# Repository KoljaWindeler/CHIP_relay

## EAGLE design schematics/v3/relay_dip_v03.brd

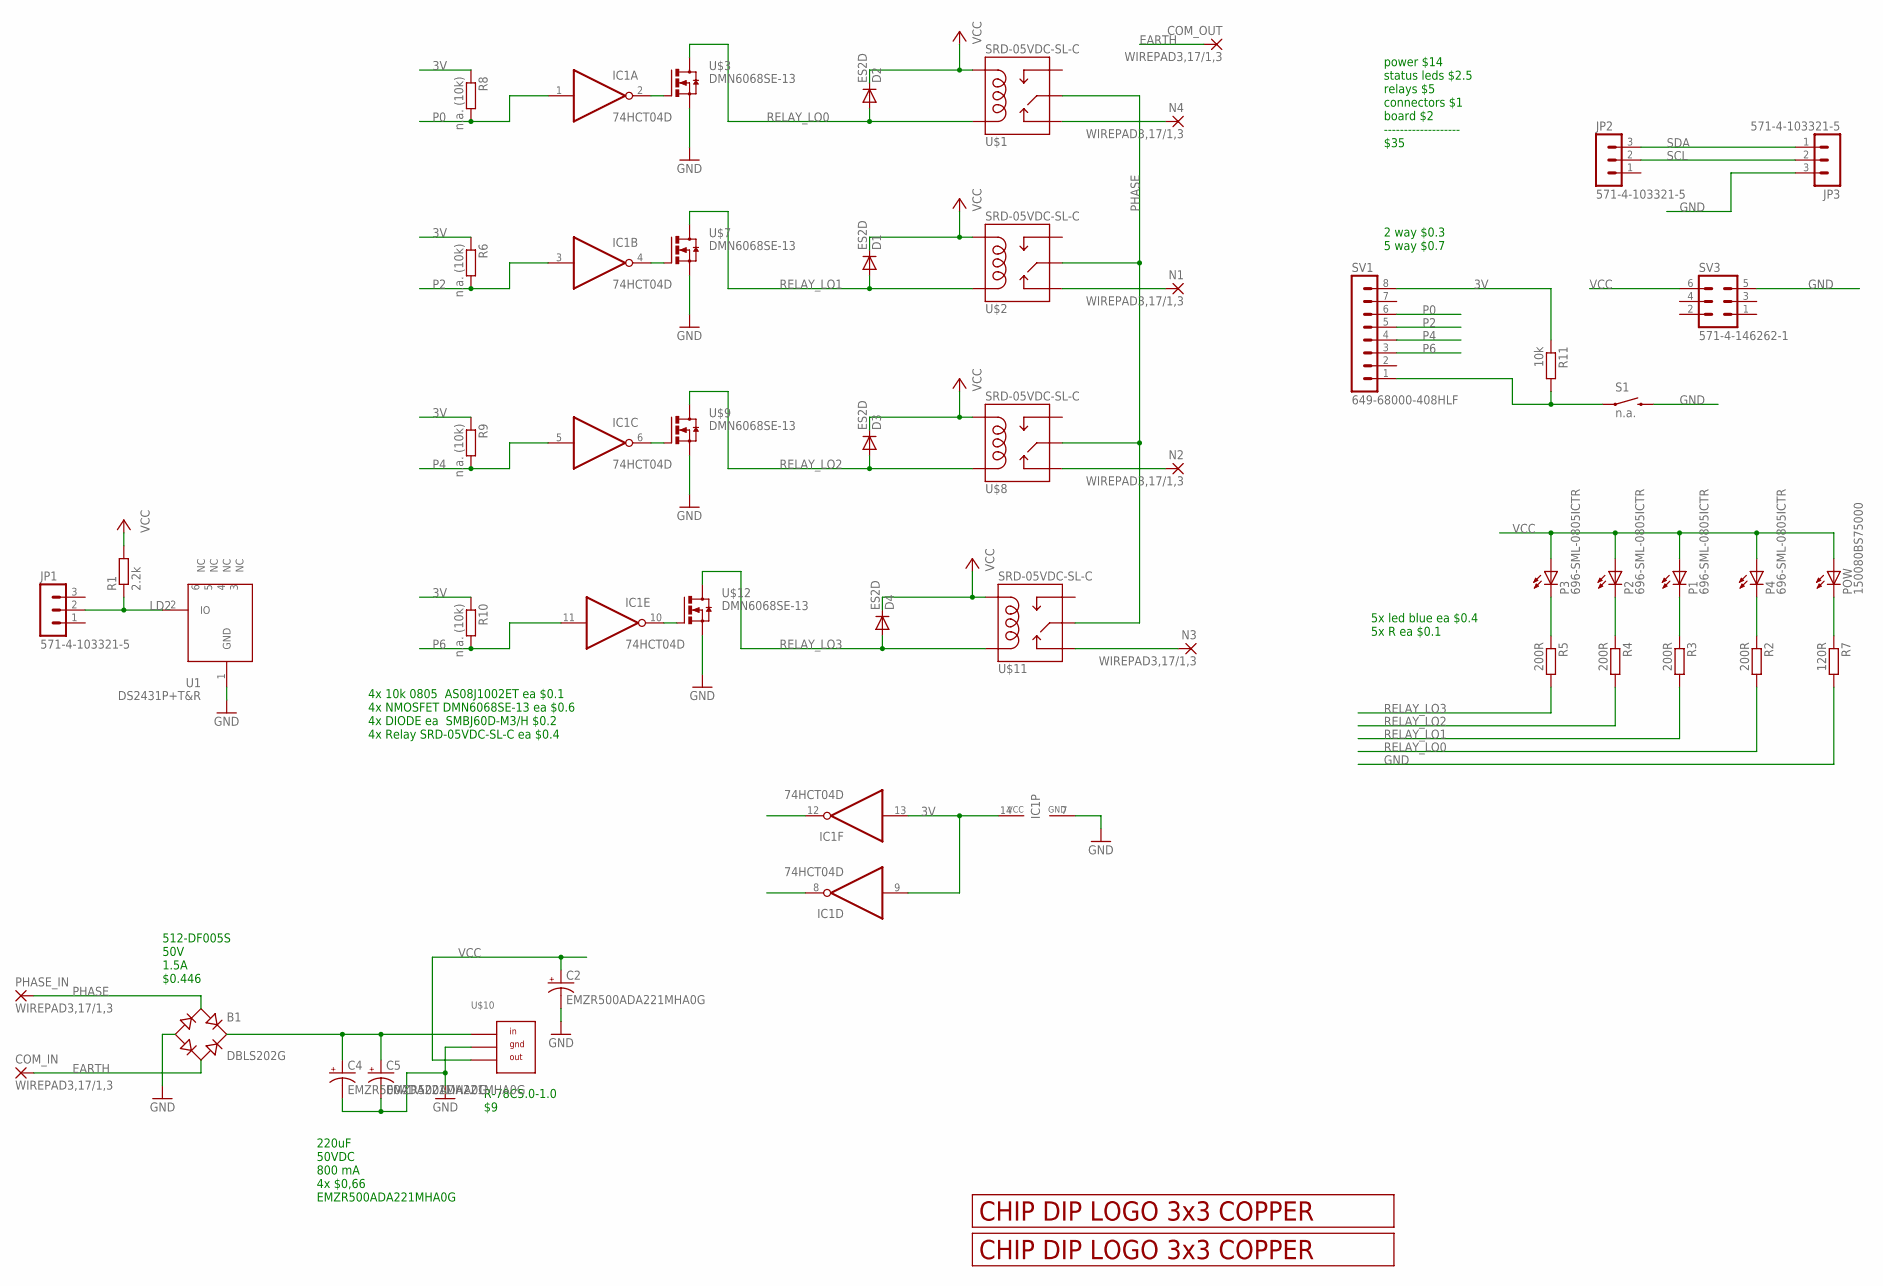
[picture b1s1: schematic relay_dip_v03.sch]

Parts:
B1: DBLS202G; DBS
C2, C4, C5: EMZR500ADA221MHA0G; 150CLZ-0810
COM_IN: WIREPAD3,17/1,3; 3,17/1,3
COM_OUT: WIREPAD3,17/1,3; 3,17/1,3
D1, D2, D3, D4: ES2D; SMB
IC1: 74HCT04D; SO14
JP1, JP2, JP3: 571-4-103321-5; MA03-1
N1, N2, N3, N4: WIREPAD3,17/1,3; 3,17/1,3
P1, P2, P3, P4: 696-SML-0805ICTR; CHIP-LED0805
PHASE_IN: WIREPAD3,17/1,3; 3,17/1,3
POW: 150080BS75000; CHIP-LED0805
R1: 2.2k; R0805
R2, R3, R4, R5: 200R; R0805
R6, R8, R9, R10: n.a. (10k); R0805
R7: 120R; R0805
R11: 10k; R0805
S1: n.a.; TACTILE-SWITCH-SMD
SV1: 649-68000-408HLF; MA08-1
SV3: 571-4-146262-1; MA03-2
U1: DS2431P+T&R; TSOC6
U$1, U$2, U$8, U$11: SRD-05VDC-SL-C
U$3, U$7, U$9, U$12: DMN6068SE-13; SOT223
U$4, U$6: LOGO_3X3_COPPER
U$10: R-7805-1.0; SIP3

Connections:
3V: IC1.9 (I), IC1.13 (I), IC1.14 (VCC), R6.1, R8.1, R9.1, R10.1, R11.1, SV1.8
EARTH: B1.AC2, COM_IN.1, COM_OUT.1
GND: B1.-, C2.-, C4.-, C5.-, IC1.7 (GND), JP3.3, R7.2, S1.3 (2), SV3.5, U1.1 (GND), U$3.3 (S), U$7.3 (S), U$9.3 (S), U$10.GND, U$12.3 (S)
LD2: JP1.2, R1.1, U1.2 (IO)
unnamed: R11.2, S1.1, SV1.1
unnamed: IC1.2 (O), U$3.1 (G)
unnamed: P4.C, R2.1
unnamed: P1.C, R3.1
unnamed: B1.+, C4.+, C5.+, U$10.IN
unnamed: IC1.4 (O), U$7.1 (G)
unnamed: P2.C, R4.1
unnamed: IC1.6 (O), U$9.1 (G)
unnamed: P3.C, R5.1
unnamed: IC1.10 (O), U$12.1 (G)
unnamed: POW.C, R7.1
NCL: N4.1, U$1.SWCLOSED (SWCLOSE)
NCL1: N1.1, U$2.SWCLOSED (SWCLOSE)
NCL2: N2.1, U$8.SWCLOSED (SWCLOSE)
NCL3: N3.1, U$11.SWCLOSED (SWCLOSE)
P0: IC1.1 (I), R8.2, SV1.6
P2: IC1.3 (I), R6.2, SV1.5
P4: IC1.5 (I), R9.2, SV1.4
P6: IC1.11 (I), R10.2, SV1.3
PHASE: B1.AC1, PHASE_IN.1, U$1.SWCOMMON, U$2.SWCOMMON, U$8.SWCOMMON, U$11.SWCOMMON
RELAY_LO0: D2.A, R2.2, U$1.COIL1, U$3.2 (D), U$3.4 (D)
RELAY_LO1: D1.A, R3.2, U$2.COIL1, U$7.2 (D), U$7.4 (D)
RELAY_LO2: D3.A, R4.2, U$8.COIL1, U$9.2 (D), U$9.4 (D)
RELAY_LO3: D4.A, R5.2, U$11.COIL1, U$12.2 (D), U$12.4 (D)
SCL: JP2.2, JP3.2
SDA: JP2.3, JP3.1
VCC: C2.+, D1.C, D2.C, D3.C, D4.C, P1.A, P2.A, P3.A, P4.A, POW.A, R1.2, SV3.6, U$1.COIL0, U$2.COIL0, U$8.COIL0, U$10.OUT, U$11.COIL0

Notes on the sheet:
220uF 50VDC 800 mA 4x $0,66 EMZR500ADA221MHA0G
512-DF005S 50V 1.5A $0.446
R-78C5.0-1.0 $9
4x 10k 0805 AS08J1002ET ea $0.1 4x NMOSFET DMN6068SE-13 ea $0.6 4x DIODE ea SMBJ60D-M3/H $0.2 4x Relay SRD-05VDC-SL-C ea $0.4
2 way $0.3 5 way $0.7
5x led blue ea $0.4 5x R ea $0.1
power $14 status leds $2.5 relays $5 connectors $1 board $2 ------------------- $35

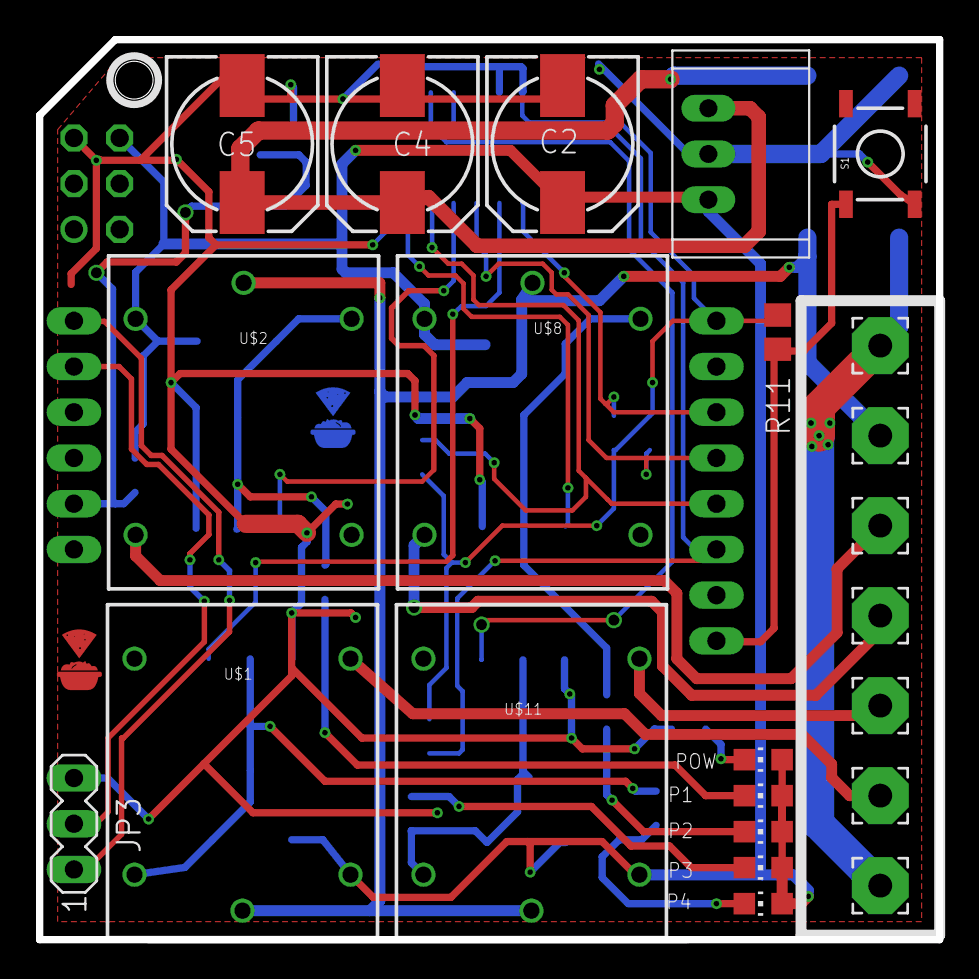
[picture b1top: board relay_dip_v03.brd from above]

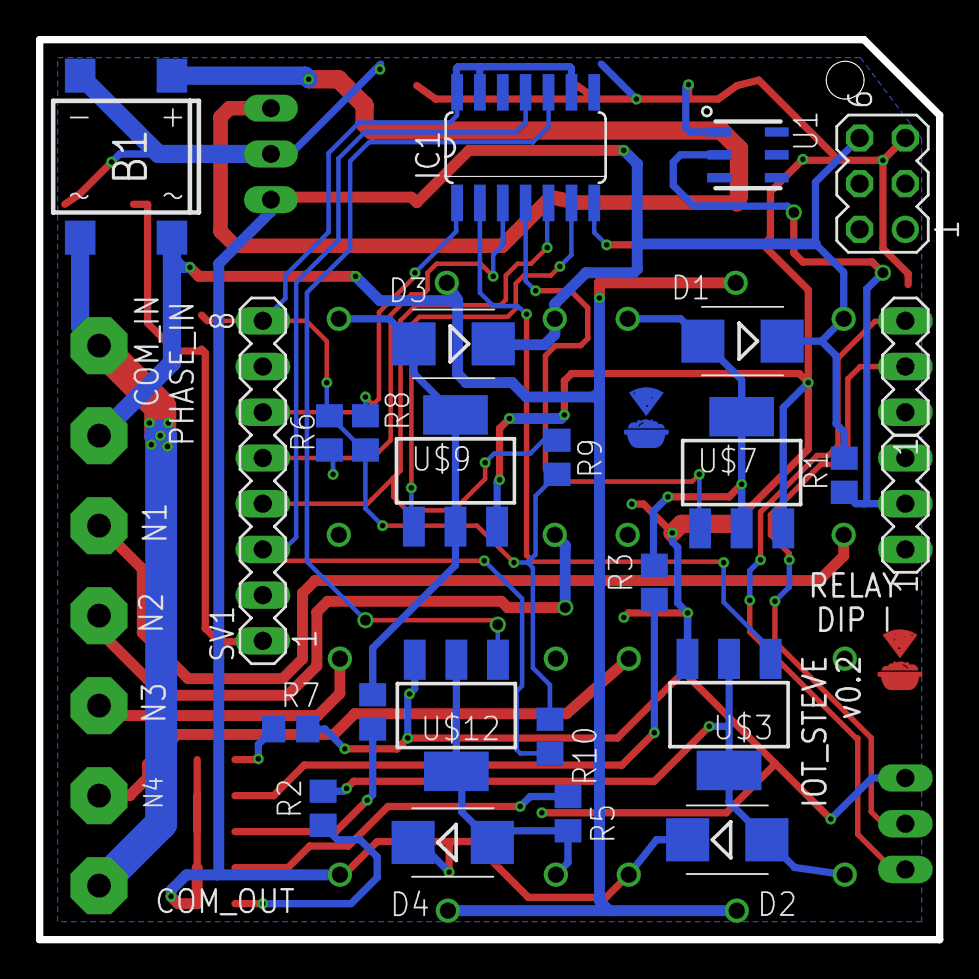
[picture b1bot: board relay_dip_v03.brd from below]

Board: 2 copper layers, 50.0 x 50.0 mm, 50 parts (26 on the bottom side), 31 nets.

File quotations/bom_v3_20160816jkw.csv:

Qty;Value;Device;Package;Parts;Description;ASSEMBLE;DESCRIPTION;FOOTPRINT;LINK;MF;MFG;MFG_PN;MPN;OC_FARNELL;OC_NEWARK;PART_TYPE;PRICE;PROD_ID;TOLLERANCE;VENDOR;VENDOR_PART_NUMBER
1;10k;R-EU_R0805;R0805;R11;RESISTOR, European symbol;;;;;;;;;;;;;;;;
1;120R;R-EU_R0805;R0805;R7;RESISTOR, European symbol;;;;;;;;;;;;;;;;
1;150080BS75000;LEDCHIP-LED0805;CHIP-LED0805;POW;LED;;;;;;;;;;;;;;;;
1;2.2k;R-EU_R0805;R0805;R1;RESISTOR, European symbol;;;;;;;;;;;;;;;;
4;200R;R-EU_R0805;R0805;R2, R3, R4, R5;RESISTOR, European symbol;;;;;;;;;;;;;;;;
3;571-4-103321-5;MA03-1;MA03-1;JP1, JP2, JP3;PIN HEADER;;;;;;;;;unknown;unknown;;;;;;
1;571-4-146262-1;MA03-2;MA03-2;SV3;PIN HEADER;;;;;;;;;unknown;unknown;;;;;;
1;649-68000-408HLF;MA08-1;MA08-1;SV4;PIN HEADER;;;;;;;;;unknown;unknown;;;;;;
4;696-SML-0805ICTR;LEDCHIP-LED0805;CHIP-LED0805;P1, P2, P3, P4;LED;;;;;;;;;;;;;;;;
1;74HCT04D;74HCT04D;SO14;IC1;Hex INVERTER;;;;;;;;;;;;;;;;
1;DBLS202G;DBLS202G;DBS;B1;Single Phase 1.0 AMP Glass Passivated Bridge Rectifier;;;;;;;;;;;;;;;;
4;DMN6068SE-13;NMOSFET_SMD_223;SOT223;U$3, U$7, U$9, U$12;;;;;;;;;;;;;;;;;
1;DS2431P+T&R;DS2431P;TSOC6;U1;1024-Bit EEPROM;;IC, 1024-Bit, 1-Wire EEPROM, TSOC6;TSOC6;http://www.digikey.com/product-detail/en/DS2431P%2BT%26R/DS2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;;DIGIKEY;DS2431P+T&RCT-ND;;;;IC;0.98;;;MAXIM;DS2431P+T&R
3;EMZR500ADA221MHA0G;CPOL-US150CLZ-0810;150CLZ-0810;C2, C4, C5;POLARIZED CAPACITOR, American symbol;;;;;;;;;;;;;;;;
4;ES2D;DIODE-SMB;SMB;D1, D2, D3, D4;DIODE;;;;;;;;;;;;;;;;
1;R-7805-1.0;R-7805-1.0;SIP3;U$10;;;;;;;;;;;;;;;;;
4;SRD-05VDC-SL-C;RELAYPTH;SRD-05VDC-SL-C;U$1, U$2, U$8, U$11;SPDT relay (COM-00101);;;;;;;;;;;;;;;;

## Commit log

2016-06-09 :octocat: Added .gitattributes
2016-06-09 init
2016-06-16 moved files to subfolder
2016-07-18 moved v2 to dedicated folder, ordered boards
2016-07-19 ordered design
2016-07-21 moved libs, dru, cam to common
2016-08-02 added v3, fixed ds2431 footprint, added quotation
2016-08-03 added test python for chip-io
2016-08-03 improved script
2016-08-16 updated quotiation, bom and ger
2016-09-18 moved relays apart
2016-09-20 flipped pin header to lower layer
2016-10-11 moved switch further outside
2016-11-27 updated ger
2017-02-10 added designators

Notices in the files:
parts and their libraries:
SparkFun-Electromechanical: Licensing: Creative Commons ShareAlike 4.0 International - https://creativecommons.org/licenses/by-sa/4.0
